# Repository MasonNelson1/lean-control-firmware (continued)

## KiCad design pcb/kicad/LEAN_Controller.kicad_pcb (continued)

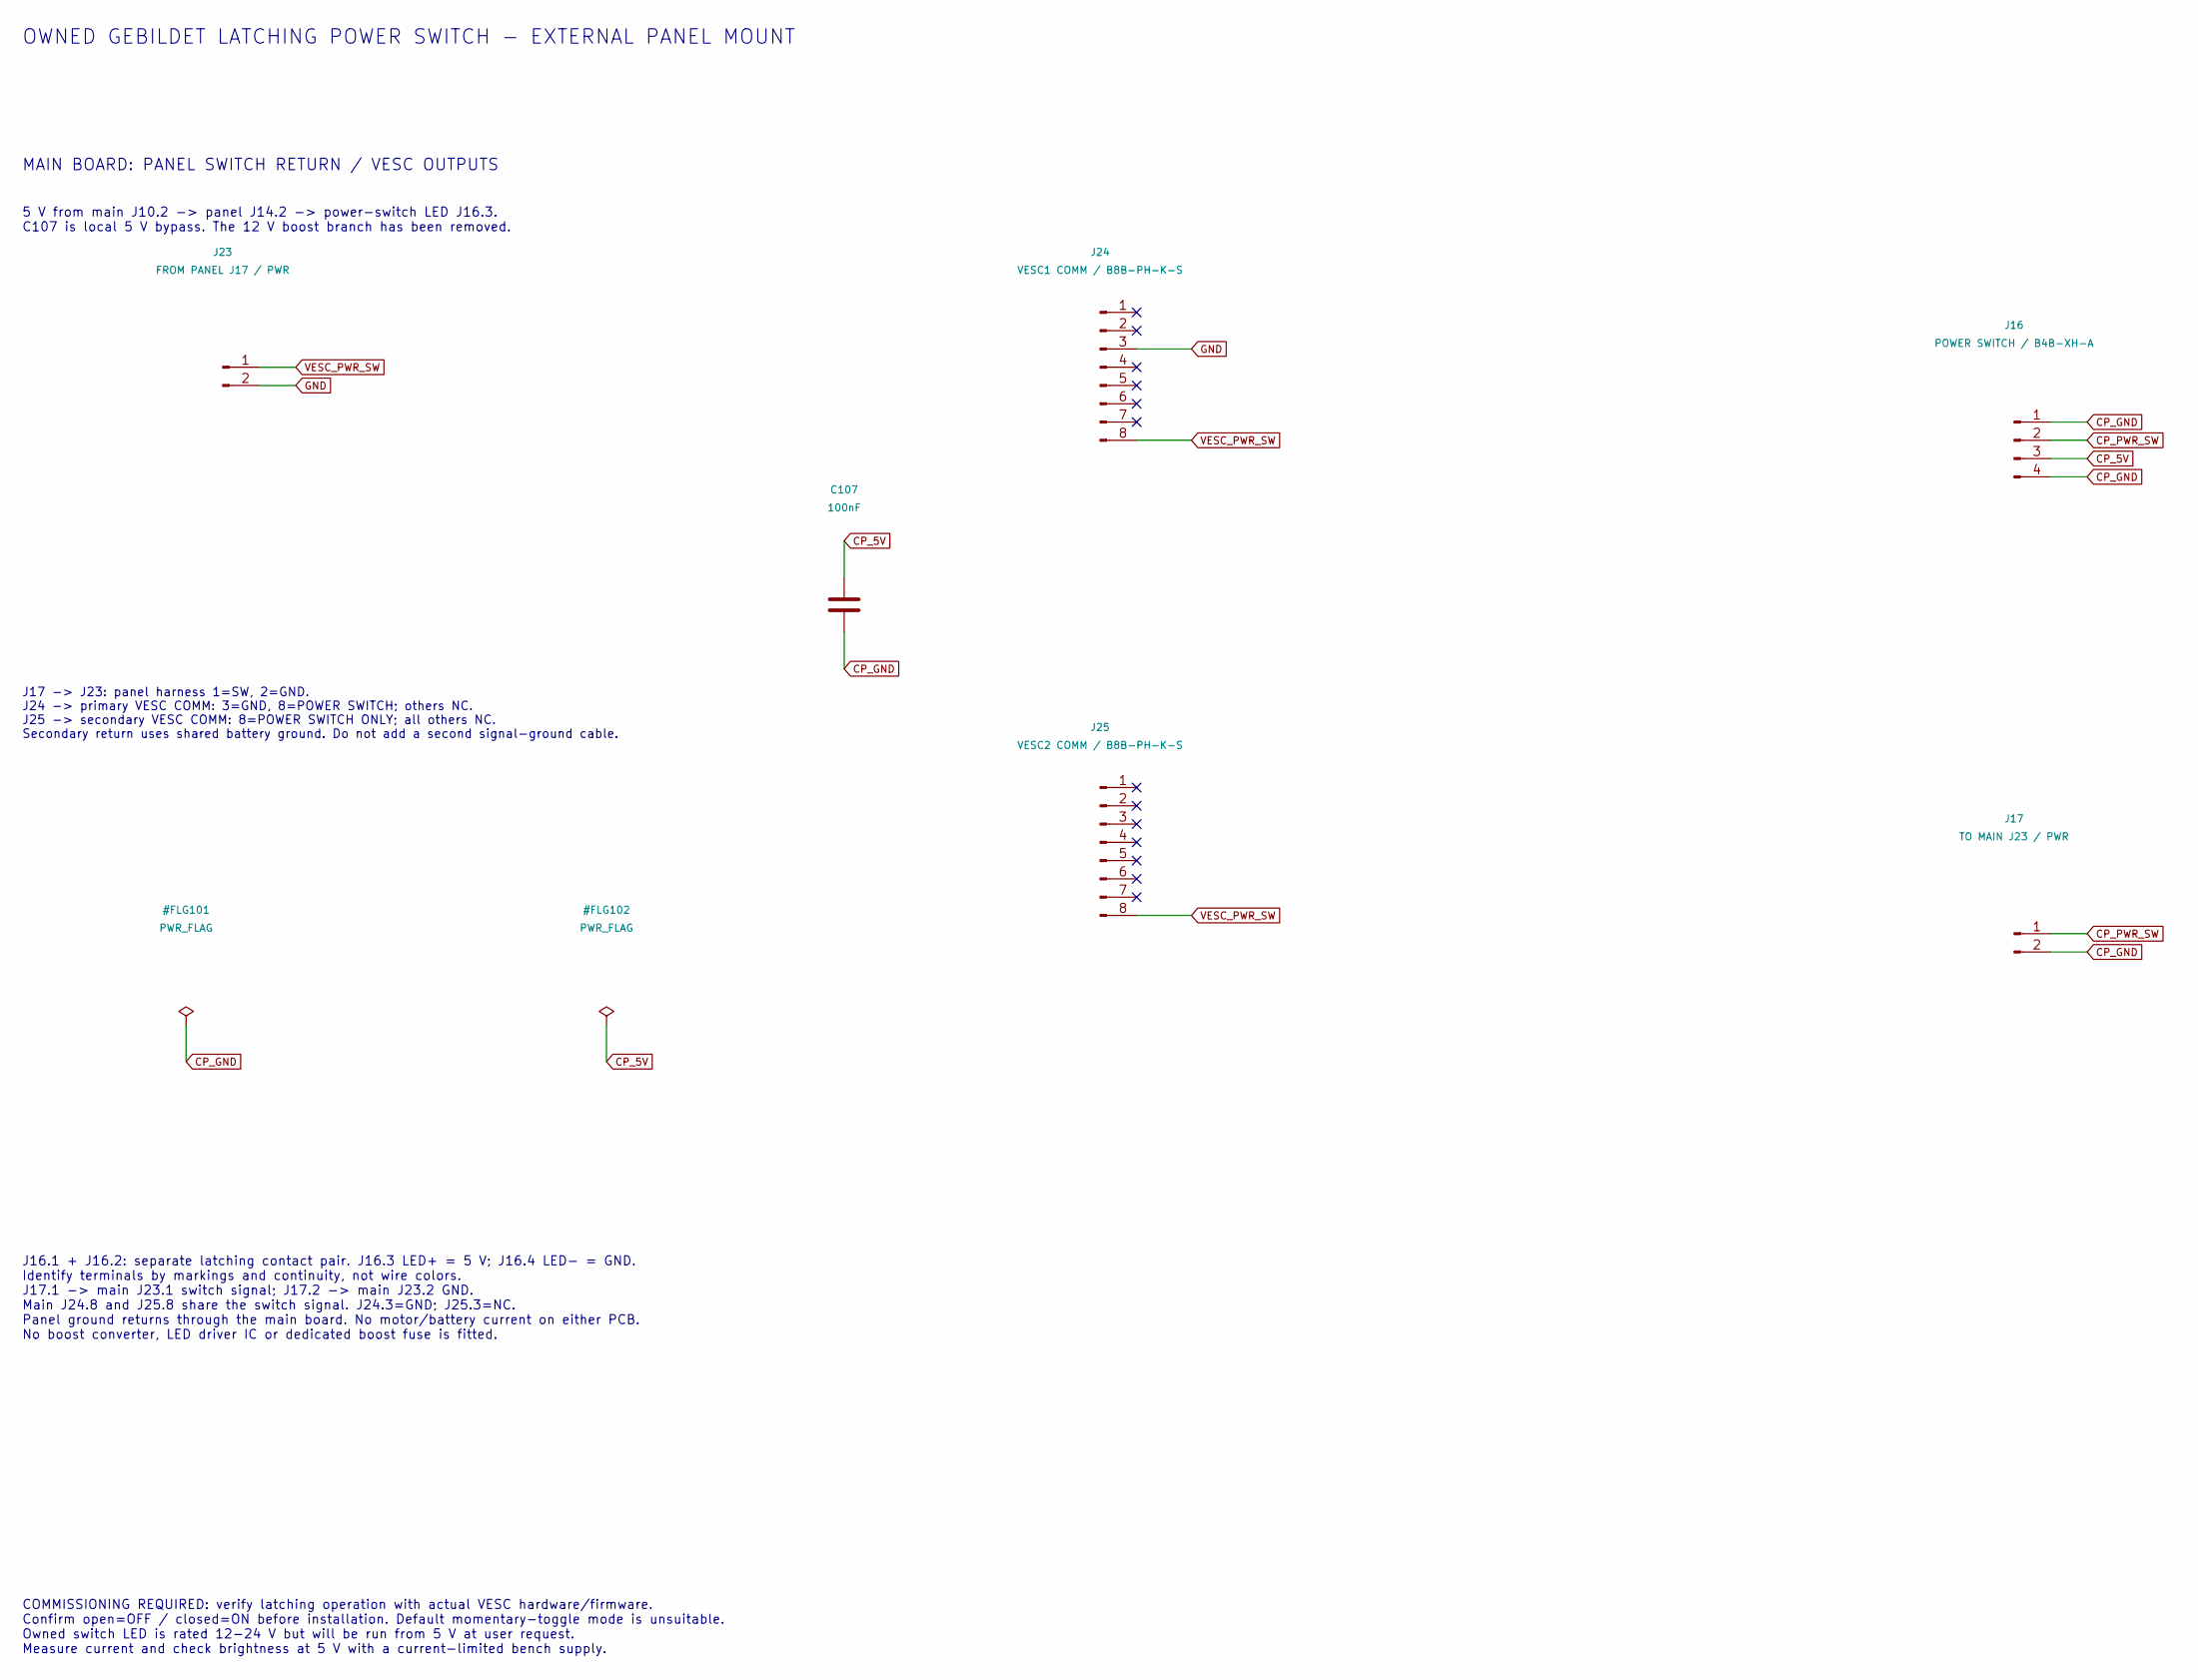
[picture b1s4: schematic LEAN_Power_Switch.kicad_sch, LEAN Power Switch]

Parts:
C107: 100nF; C_Disc_D5.0mm_W2.5mm_P5.00mm
J16: POWER SWITCH / B4B-XH-A; JST_XH_B4B-XH-A_1x04_P2.50mm_Vertical
J17: TO MAIN J23 / PWR; JST_PH_B2B-PH-K_1x02_P2.00mm_Vertical
J23: FROM PANEL J17 / PWR; JST_PH_B2B-PH-K_1x02_P2.00mm_Vertical
J24: VESC1 COMM / B8B-PH-K-S; JST_PH_B8B-PH-K_1x08_P2.00mm_Vertical
J25: VESC2 COMM / B8B-PH-K-S; JST_PH_B8B-PH-K_1x08_P2.00mm_Vertical

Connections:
CP_5V: C107.1, J16.3; also elsewhere on the board
CP_GND: C107.2, J16.1, J16.4, J17.2; also elsewhere on the board
CP_PWR_SW: J16.2, J17.1
GND: J23.2, J24.3; also elsewhere on the board
VESC_PWR_SW: J23.1, J24.8, J25.8

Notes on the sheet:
OWNED GEBILDET LATCHING POWER SWITCH - EXTERNAL PANEL MOUNT
J16.1 + J16.2: separate latching contact pair. J16.3 LED+ = 5 V; J16.4 LED- = GND. Identify terminals by markings and continuity, not wire colors. J17.1 -> main J23.1 switch signal; J17.2 -> main J23.2 GND. Main J24.8 and J25.8 share the switch signal. J24.3=GND; J25.3=NC. Panel ground returns thro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
COMMISSIONING REQUIRED: verify latching operation with actual VESC hardware/firmware. Confirm open=OFF / closed=ON before installation. Default momentary-toggle mode is unsuitable. Owned switch LED is rated 12-24 V but will be run from 5 V at user request. Measure current and check brightness at 5 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
5 V from main J10.2 -> panel J14.2 -> power-switch LED J16.3. C107 is local 5 V bypass. The 12 V boost branch has been removed.
MAIN BOARD: PANEL SWITCH RETURN / VESC OUTPUTS
J17 -> J23: panel harness 1=SW, 2=GND. J24 -> primary VESC COMM: 3=GND, 8=POWER SWITCH; others NC. J25 -> secondary VESC COMM: 8=POWER SWITCH ONLY; all others NC. Secondary return uses shared battery ground. Do not add a second signal-ground cable.

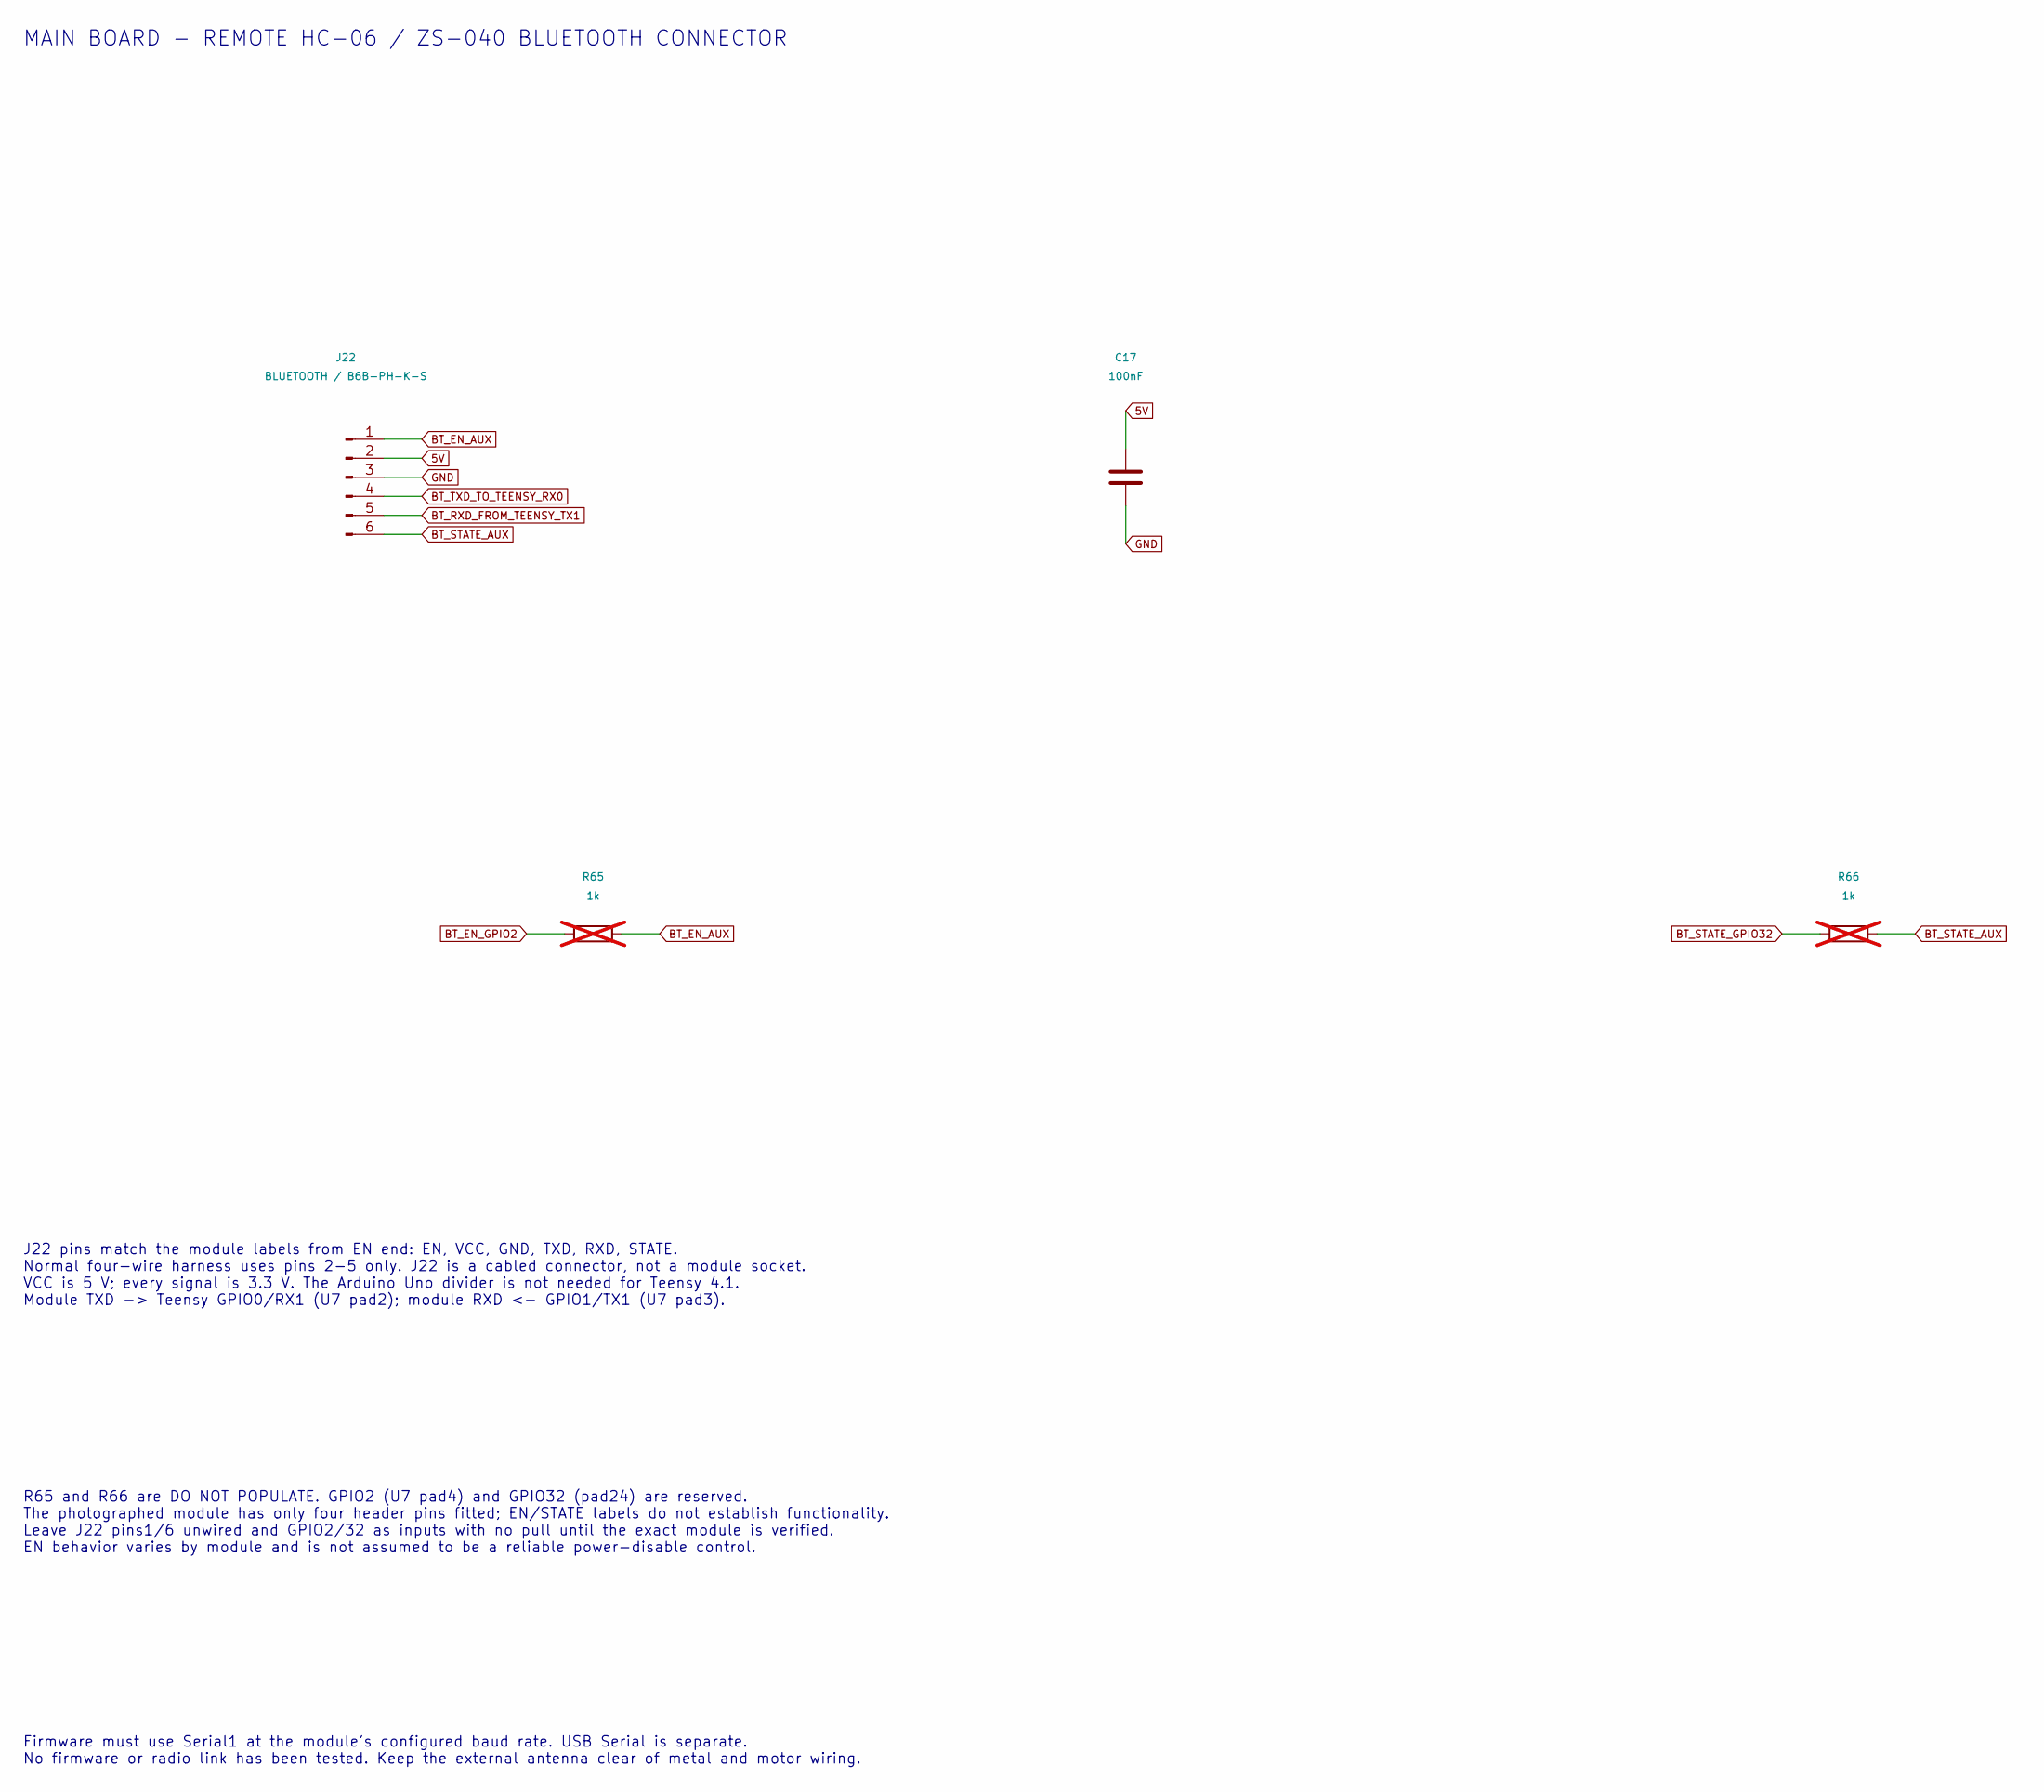
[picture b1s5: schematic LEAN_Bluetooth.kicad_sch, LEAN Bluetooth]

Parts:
C17: 100nF; C_Disc_D5.0mm_W2.5mm_P5.00mm
J22: BLUETOOTH / B6B-PH-K-S; JST_PH_B6B-PH-K_1x06_P2.00mm_Vertical
R65, R66: 1k; R_Axial_DIN0207_L6.3mm_D2.5mm_P7.62mm_Horizontal; not fitted

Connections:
5V: C17.1, J22.2; also elsewhere on the board
BT_EN_AUX: J22.1, R65.2
BT_EN_GPIO2: R65.1; also elsewhere on the board
BT_RXD_FROM_TEENSY_TX1: J22.5; also elsewhere on the board
BT_STATE_AUX: J22.6, R66.2
BT_STATE_GPIO32: R66.1; also elsewhere on the board
BT_TXD_TO_TEENSY_RX0: J22.4; also elsewhere on the board
GND: C17.2, J22.3; also elsewhere on the board

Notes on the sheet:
MAIN BOARD - REMOTE HC-06 / ZS-040 BLUETOOTH CONNECTOR
J22 pins match the module labels from EN end: EN, VCC, GND, TXD, RXD, STATE. Normal four-wire harness uses pins 2-5 only. J22 is a cabled connector, not a module socket. VCC is 5 V; every signal is 3.3 V. The Arduino Uno divider is not needed for Teensy 4.1. Module TXD -> Teensy GPIO0/RX1 (U7 pad2)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
R65 and R66 are DO NOT POPULATE. GPIO2 (U7 pad4) and GPIO32 (pad24) are reserved. The photographed module has only four header pins fitted; EN/STATE labels do not establish functionality. Leave J22 pins1/6 unwired and GPIO2/32 as inputs with no pull until the exact module is verified. EN behavior v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
Firmware must use Serial1 at the module's configured baud rate. USB Serial is separate. No firmware or radio link has been tested. Keep the external antenna clear of metal and motor wiring.

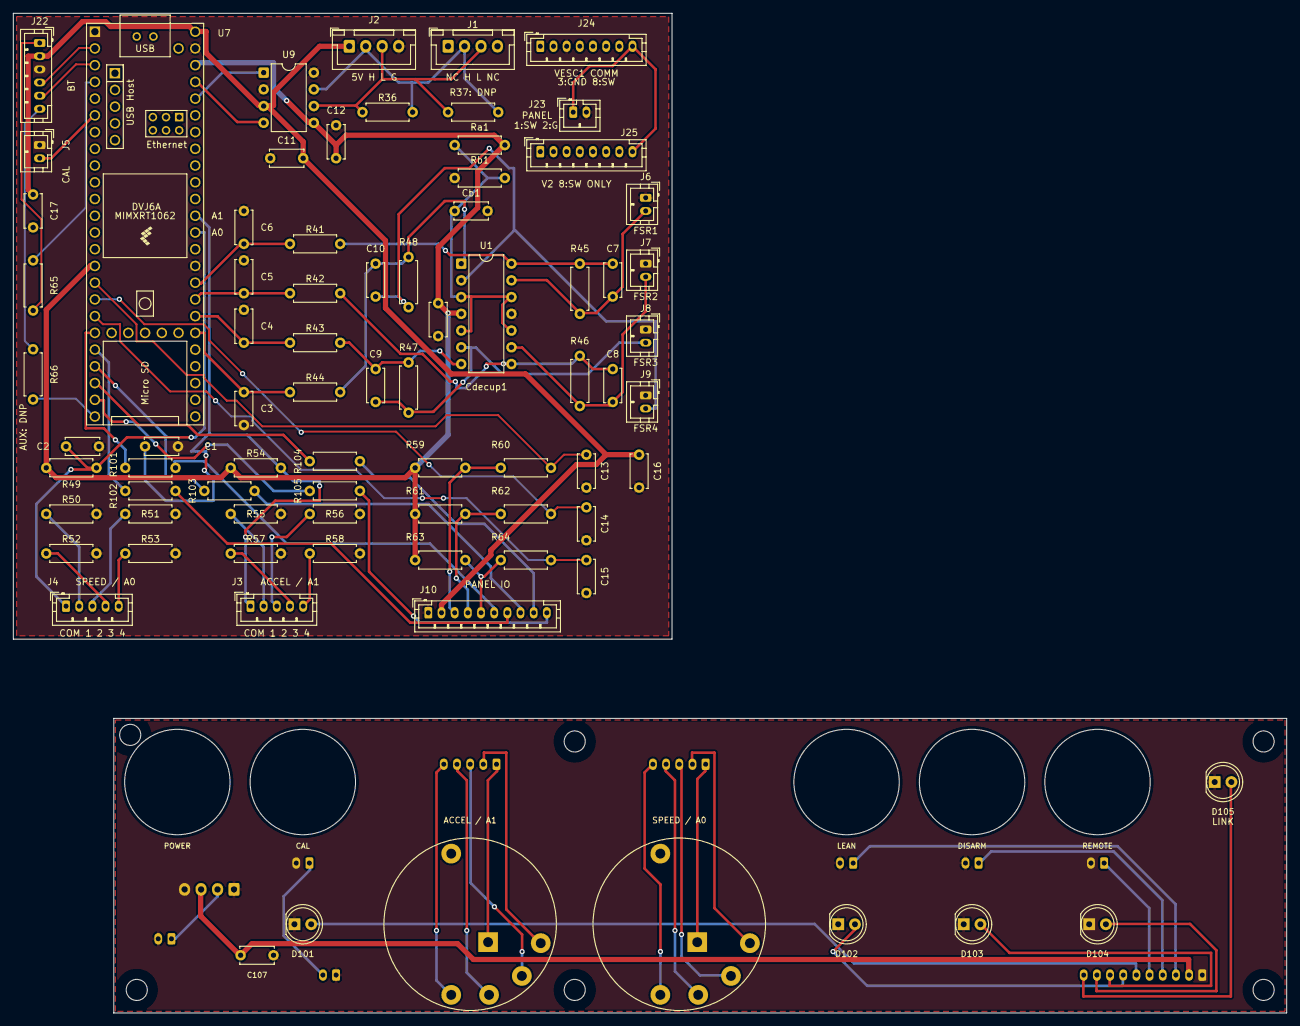
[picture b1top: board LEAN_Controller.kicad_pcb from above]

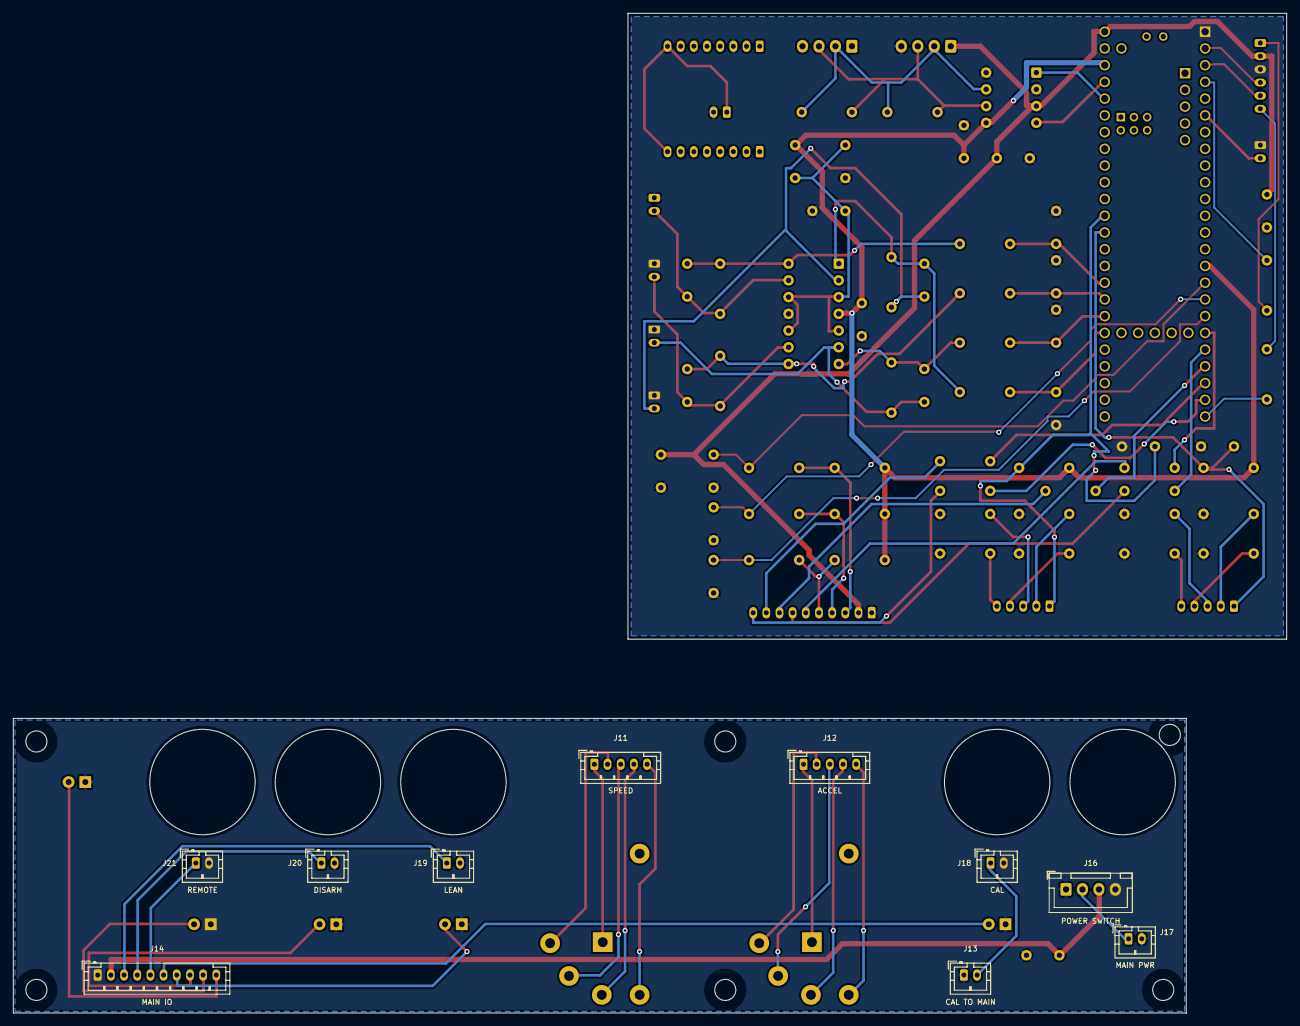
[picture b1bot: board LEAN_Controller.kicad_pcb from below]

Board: 2 copper layers, 193.3 x 151.8 mm, 95 parts (10 on the bottom side), 76 nets.

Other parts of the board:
H101, H102, H103, H104, H105, H106: MountingHole_3.2mm

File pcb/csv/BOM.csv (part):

Reference,Board,Side,Value,Footprint,Assembly,Tolerance,Notes
C1,Main controller,Front,100nF,C_Disc_D5.0mm_W2.5mm_P5.00mm,Fit,,
C2,Main controller,Front,100nF,C_Disc_D5.0mm_W2.5mm_P5.00mm,Fit,,
C3,Main controller,Front,10nF,C_Disc_D5.0mm_W2.5mm_P5.00mm,Fit,,
C4,Main controller,Front,10nF,C_Disc_D5.0mm_W2.5mm_P5.00mm,Fit,,
C5,Main controller,Front,10nF,C_Disc_D5.0mm_W2.5mm_P5.00mm,Fit,,
C6,Main controller,Front,10nF,C_Disc_D5.0mm_W2.5mm_P5.00mm,Fit,,
C7,Main controller,Front,1nF,C_Disc_D5.0mm_W2.5mm_P5.00mm,Fit,,
C8,Main controller,Front,1nF,C_Disc_D5.0mm_W2.5mm_P5.00mm,Fit,,
C9,Main controller,Front,1nF,C_Disc_D5.0mm_W2.5mm_P5.00mm,Fit,,
C10,Main controller,Front,1nF,C_Disc_D5.0mm_W2.5mm_P5.00mm,Fit,,
C11,Main controller,Front,0.1uF,C_Disc_D5.0mm_W2.5mm_P5.00mm,Fit,,
C12,Main controller,Front,0.1uF,C_Disc_D5.0mm_W2.5mm_P5.00mm,Fit,,
C13,Main controller,Front,100nF,C_Disc_D5.0mm_W2.5mm_P5.00mm,Fit,,
C14,Main controller,Front,100nF,C_Disc_D5.0mm_W2.5mm_P5.00mm,Fit,,
C15,Main controller,Front,100nF,C_Disc_D5.0mm_W2.5mm_P5.00mm,Fit,,
C16,Main controller,Front,100nF,C_Disc_D5.0mm_W2.5mm_P5.00mm,Fit,,
C17,Main controller,Front,100nF,C_Disc_D5.0mm_W2.5mm_P5.00mm,Fit,,100 nF 5 V supply bypass beside Bluetooth connector; lab stock suitable.
C107,Control panel,Front,100nF,C_Disc_D5.0mm_W2.5mm_P5.00mm,Fit,,Local 100 nF bypass across panel 5 V and GND.
Cb1,Main controller,Front,1uF,C_Disc_D5.0mm_W2.5mm_P5.00mm,Fit,,
Cdecup1,Main controller,Front,0.1uF,C_Disc_D5.0mm_W2.5mm_P5.00mm,Fit,,
D101,Control panel,Front,WP7113LID / CAL,LED_D5.0mm,Fit,,5 mm low-current red indicator; WP7113LID or lab-stock equivalent verified for brightness at about 1-2 mA and matching polarity/footprint.
D102,Control panel,Front,WP7113LID / LEAN,LED_D5.0mm,Fit,,5 mm low-current red indicator; WP7113LID or lab-stock equivalent verified for brightness at about 1-2 mA and matching polarity/footprint.
D103,Control panel,Front,WP7113LID / DISARM,LED_D5.0mm,Fit,,5 mm low-current red indicator; WP7113LID or lab-stock equivalent verified for brightness at about 1-2 mA and matching polarity/footprint.
D104,Control panel,Front,WP7113LID / REMOTE,LED_D5.0mm,Fit,,5 mm low-current red indicator; WP7113LID or lab-stock equivalent verified for brightness at about 1-2 mA and matching polarity/footprint.
D105,Control panel,Front,WP7113LID / CONNECTED,LED_D5.0mm,Fit,,5 mm low-current red indicator; WP7113LID or lab-stock equivalent verified for brightness at about 1-2 mA and matching polarity/footprint.
J1,Main controller,Front,B4B-XH-A,JST_XH_B4B-XH-A_1x04_P2.50mm_Vertical,Fit,,"1=NC, 2=CANH, 3=CANL, 4=NC; same header as J2; no secondary supply/ground"
J2,Main controller,Front,B4B-XH-A,JST_XH_B4B-XH-A_1x04_P2.50mm_Vertical,Fit,,
J3,Main controller,Front,B5B-PH-K-S,JST_PH_B5B-PH-K_1x05_P2.00mm_Vertical,Fit,,
J4,Main controller,Front,B5B-PH-K-S,JST_PH_B5B-PH-K_1x05_P2.00mm_Vertical,Fit,,
J5,Main controller,Front,B2B-PH-K-S,JST_PH_B2B-PH-K_1x02_P2.00mm_Vertical,Fit,,
J6,Main controller,Front,B2B-PH-K-S,JST_PH_B2B-PH-K_1x02_P2.00mm_Vertical,Fit,,
J7,Main controller,Front,B2B-PH-K-S,JST_PH_B2B-PH-K_1x02_P2.00mm_Vertical,Fit,,
J8,Main controller,Front,B2B-PH-K-S,JST_PH_B2B-PH-K_1x02_P2.00mm_Vertical,Fit,,
J9,Main controller,Front,B2B-PH-K-S,JST_PH_B2B-PH-K_1x02_P2.00mm_Vertical,Fit,,
J10,Main controller,Front,PANEL_IO / B10B-PH-K-S,JST_PH_B10B-PH-K_1x10_P2.00mm_Vertical,Fit,,
J11,Control panel,Back,TO MAIN J4,JST_PH_B5B-PH-K_1x05_P2.00mm_Vertical,Fit,,MOUNT ON BACK. Use pad numbers and keyed housing; rear view mirrors the front.
J12,Control panel,Back,TO MAIN J3,JST_PH_B5B-PH-K_1x05_P2.00mm_Vertical,Fit,,MOUNT ON BACK. Use pad numbers and keyed housing; rear view mirrors the front.
J13,Control panel,Back,TO MAIN J5 / CAL,JST_PH_B2B-PH-K_1x02_P2.00mm_Vertical,Fit,,MOUNT ON BACK. Use pad numbers and keyed housing; rear view mirrors the front.
J14,Control panel,Back,TO MAIN J10 / IO,JST_PH_B10B-PH-K_1x10_P2.00mm_Vertical,Fit,,MOUNT ON BACK. Use pad numbers and keyed housing; rear view mirrors the front.
J16,Control panel,Back,POWER SWITCH / B4B-XH-A,JST_XH_B4B-XH-A_1x04_P2.50mm_Vertical,Fit,,MOUNT ON BACK. Use pad numbers and keyed housing; rear view mirrors the front.
J17,Control panel,Back,TO MAIN J23 / PWR,JST_PH_B2B-PH-K_1x02_P2.00mm_Vertical,Fit,,Pin 1 switch signal; pin 2 GND. Straight-through cable to main J23.
J18,Control panel,Back,REAR / CAL,JST_PH_B2B-PH-K_1x02_P2.00mm_Vertical,Fit,,MOUNT ON BACK. Use pad numbers and keyed housing; rear view mirrors the front.
J19,Control panel,Back,REAR / LEAN,JST_PH_B2B-PH-K_1x02_P2.00mm_Vertical,Fit,,MOUNT ON BACK. Use pad numbers and keyed housing; rear view mirrors the front.
J20,Control panel,Back,REAR / DISARM,JST_PH_B2B-PH-K_1x02_P2.00mm_Vertical,Fit,,MOUNT ON BACK. Use pad numbers and keyed housing; rear view mirrors the front.
J21,Control panel,Back,REAR / REMOTE,JST_PH_B2B-PH-K_1x02_P2.00mm_Vertical,Fit,,MOUNT ON BACK. Use pad numbers and keyed housing; rear view mirrors the front.
J22,Main controller,Front,BLUETOOTH / B6B-PH-K-S,JST_PH_B6B-PH-K_1x06_P2.00mm_Vertical,Fit,,Bluetooth cable header. Pins 2-5 used now; 1 and 6 reserved. Mating housing PHR-6.
R36,Main controller,Front,120,R_Axial_DIN0207_L6.3mm_D2.5mm_P7.62mm_Horizontal,Fit if CAN endpoint requires termination,,
R37,Main controller,Front,120,R_Axial_DIN0207_L6.3mm_D2.5mm_P7.62mm_Horizontal,DO NOT FIT,,
R41,Main controller,Front,1k,R_Axial_DIN0207_L6.3mm_D2.5mm_P7.62mm_Horizontal,Fit,,
R42,Main controller,Front,1k,R_Axial_DIN0207_L6.3mm_D2.5mm_P7.62mm_Horizontal,Fit,,
R43,Main controller,Front,1k,R_Axial_DIN0207_L6.3mm_D2.5mm_P7.62mm_Horizontal,Fit,,
R44,Main controller,Front,1k,R_Axial_DIN0207_L6.3mm_D2.5mm_P7.62mm_Horizontal,Fit,,
R45,Main controller,Front,47k,R_Axial_DIN0207_L6.3mm_D2.5mm_P7.62mm_Horizontal,Fit,,
R46,Main controller,Front,47k,R_Axial_DIN0207_L6.3mm_D2.5mm_P7.62mm_Horizontal,Fit,,
R47,Main controller,Front,47k,R_Axial_DIN0207_L6.3mm_D2.5mm_P7.62mm_Horizontal,Fit,,
R48,Main controller,Front,47k,R_Axial_DIN0207_L6.3mm_D2.5mm_P7.62mm_Horizontal,Fit,,
R49,Main controller,Front,4.7k,R_Axial_DIN0207_L6.3mm_D2.5mm_P7.62mm_Horizontal,Fit,1%,"0.25 W axial, 7.62 mm lead spacing; rotary input network"
R50,Main controller,Front,1k,R_Axial_DIN0207_L6.3mm_D2.5mm_P7.62mm_Horizontal,Fit,1%,"0.25 W axial, 7.62 mm lead spacing; rotary input network"
R51,Main controller,Front,2.2k,R_Axial_DIN0207_L6.3mm_D2.5mm_P7.62mm_Horizontal,Fit,1%,"0.25 W axial, 7.62 mm lead spacing; rotary input network"
R52,Main controller,Front,4.7k,R_Axial_DIN0207_L6.3mm_D2.5mm_P7.62mm_Horizontal,Fit,1%,"0.25 W axial, 7.62 mm lead spacing; rotary input network"
R53,Main controller,Front,10k,R_Axial_DIN0207_L6.3mm_D2.5mm_P7.62mm_Horizontal,Fit,1%,"0.25 W axial, 7.62 mm lead spacing; rotary input network"
R54,Main controller,Front,4.7k,R_Axial_DIN0207_L6.3mm_D2.5mm_P7.62mm_Horizontal,Fit,1%,"0.25 W axial, 7.62 mm lead spacing; rotary input network"
R55,Main controller,Front,1k,R_Axial_DIN0207_L6.3mm_D2.5mm_P7.62mm_Horizontal,Fit,1%,"0.25 W axial, 7.62 mm lead spacing; rotary input network"
R56,Main controller,Front,2.2k,R_Axial_DIN0207_L6.3mm_D2.5mm_P7.62mm_Horizontal,Fit,1%,"0.25 W axial, 7.62 mm lead spacing; rotary input network"
R57,Main controller,Front,4.7k,R_Axial_DIN0207_L6.3mm_D2.5mm_P7.62mm_Horizontal,Fit,1%,"0.25 W axial, 7.62 mm lead spacing; rotary input network"
R58,Main controller,Front,10k,R_Axial_DIN0207_L6.3mm_D2.5mm_P7.62mm_Horizontal,Fit,1%,"0.25 W axial, 7.62 mm lead spacing; rotary input network"
R59,Main controller,Front,10k 1%,R_Axial_DIN0207_L6.3mm_D2.5mm_P7.62mm_Horizontal,Fit,1%,3.3 V button pull-up.
R60,Main controller,Front,1k,R_Axial_DIN0207_L6.3mm_D2.5mm_P7.62mm_Horizontal,Fit,,Button input series resistor; paired with 100 nF filter.
R61,Main controller,Front,10k 1%,R_Axial_DIN0207_L6.3mm_D2.5mm_P7.62mm_Horizontal,Fit,1%,3.3 V button pull-up.
R62,Main controller,Front,1k,R_Axial_DIN0207_L6.3mm_D2.5mm_P7.62mm_Horizontal,Fit,,Button input series resistor; paired with 100 nF filter.
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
